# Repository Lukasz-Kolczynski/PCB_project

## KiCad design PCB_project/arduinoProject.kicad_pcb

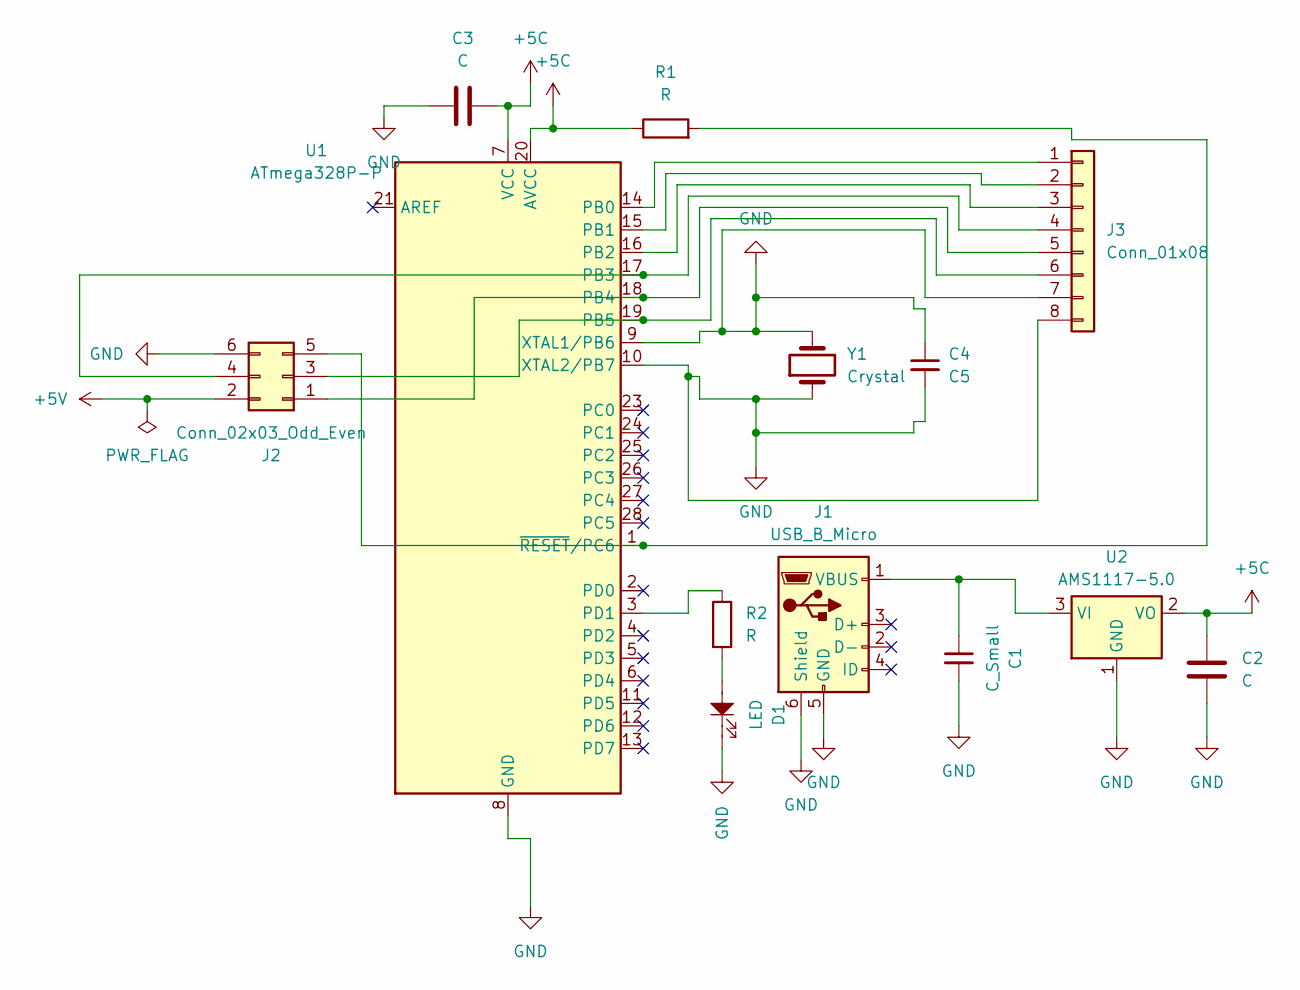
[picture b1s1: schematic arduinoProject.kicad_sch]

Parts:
C1: C_Small; C_Disc_D4.7mm_W2.5mm_P5.00mm
C2, C3: C; C_Radial_D5.0mm_H7.0mm_P2.00mm
C4: C5; C_Disc_D4.7mm_W2.5mm_P5.00mm
D1: LED; LED_D5.0mm
J1: USB_B_Micro; USB_Micro-B_Molex-105017-0001
J2: Conn_02x03_Odd_Even; PinHeader_2x03_P2.54mm_Vertical
J3: Conn_01x08; PinHeader_1x08_P2.54mm_Vertical
R1, R2: R; R_Axial_DIN0207_L6.3mm_D2.5mm_P10.16mm_Horizontal
U1: ATmega328P-P; DIP-28_W7.62mm
U2: AMS1117-5.0; SOT-223-3_TabPin2
Y1: Crystal; Crystal_HC49-U_Vertical

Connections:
+5C: C2.1, C3.2, R1.1, U1.7 (VCC), U1.20 (AVCC), U2.2 (VO)
+5V: J2.2
GND: C1.2, C2.2, C3.1, C4.1, C4.2, D1.1, J1.5 (GND), J1.6 (Shield), J2.6, J3.7, J3.8, U1.8 (GND), U1.9 (XTAL1/PB6), U1.10 (XTAL2/PB7), U1.22 (GND), U2.1 (GND), Y1.1, Y1.2
unnamed: D1.2, R2.2
unnamed: C1.1, J1.1 (VBUS), U2.3 (VI)
unnamed: J2.1, J3.5, U1.18 (PB4)
unnamed: J2.3, J3.6, U1.19 (PB5)
unnamed: J2.4, J3.4, U1.17 (PB3)
unnamed: J2.5, R1.2, U1.1 (~RESET/PC6)
unnamed: J3.1, U1.14 (PB0)
unnamed: J3.2, U1.15 (PB1)
unnamed: J3.3, U1.16 (PB2)
unnamed: R2.1, U1.3 (PD1)

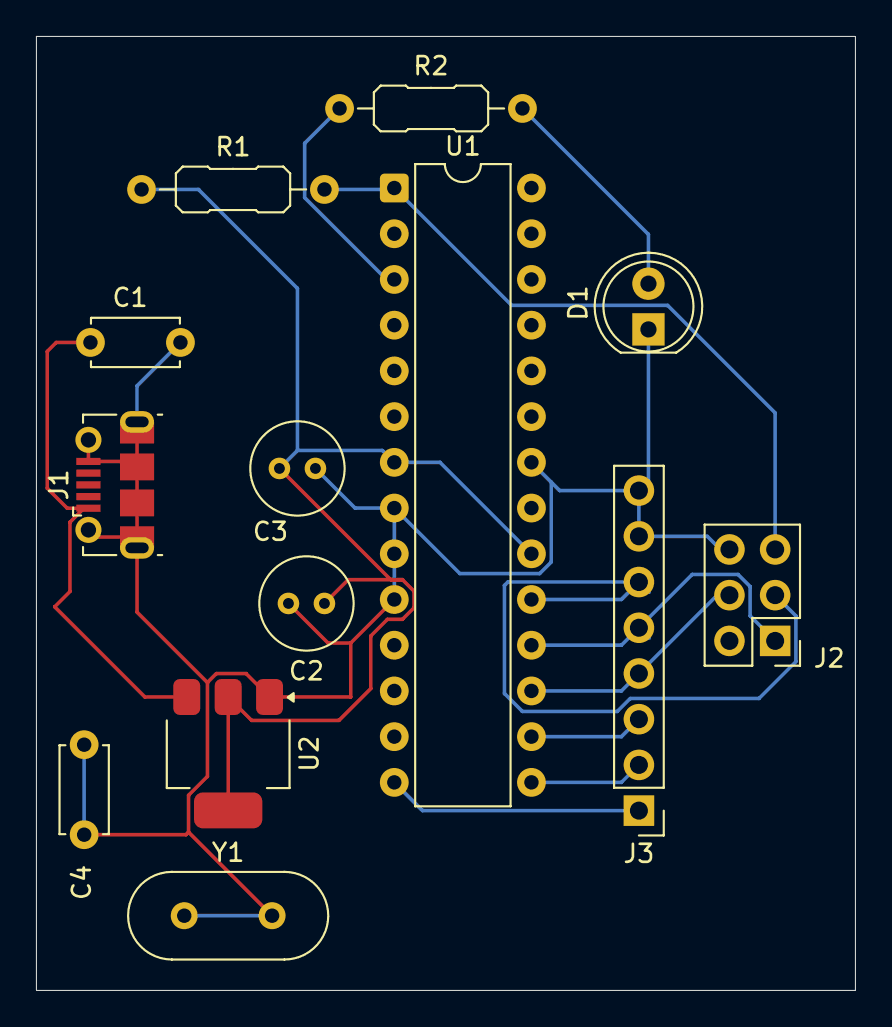
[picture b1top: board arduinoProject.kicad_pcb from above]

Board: 2 copper layers, 45.5 x 53.0 mm, 13 parts (0 on the bottom side), 12 nets.

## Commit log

2026-01-12 LedControl
